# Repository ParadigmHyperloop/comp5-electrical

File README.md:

# comp5-electrical
All schematics and layouts in KiCad, plus some simulations https://paradigmhyperloop.com

License
See the LICENSE for full licensing details.

In summary, (you still need to read the whole thing), these boards are for Paradigm, and Paradigm only. It is shared with the world for the benefit of observers and potential Paradigm team members. If you wish to utilize these designs in any way, you must contact us first and receive written permission to utilize the designs for the purpose you require.

We don't want to be restrictive, and we will almost certainly grant you permission, but we want to know what you are using our designs for, and we want to make sure you are using them correctly and safely.

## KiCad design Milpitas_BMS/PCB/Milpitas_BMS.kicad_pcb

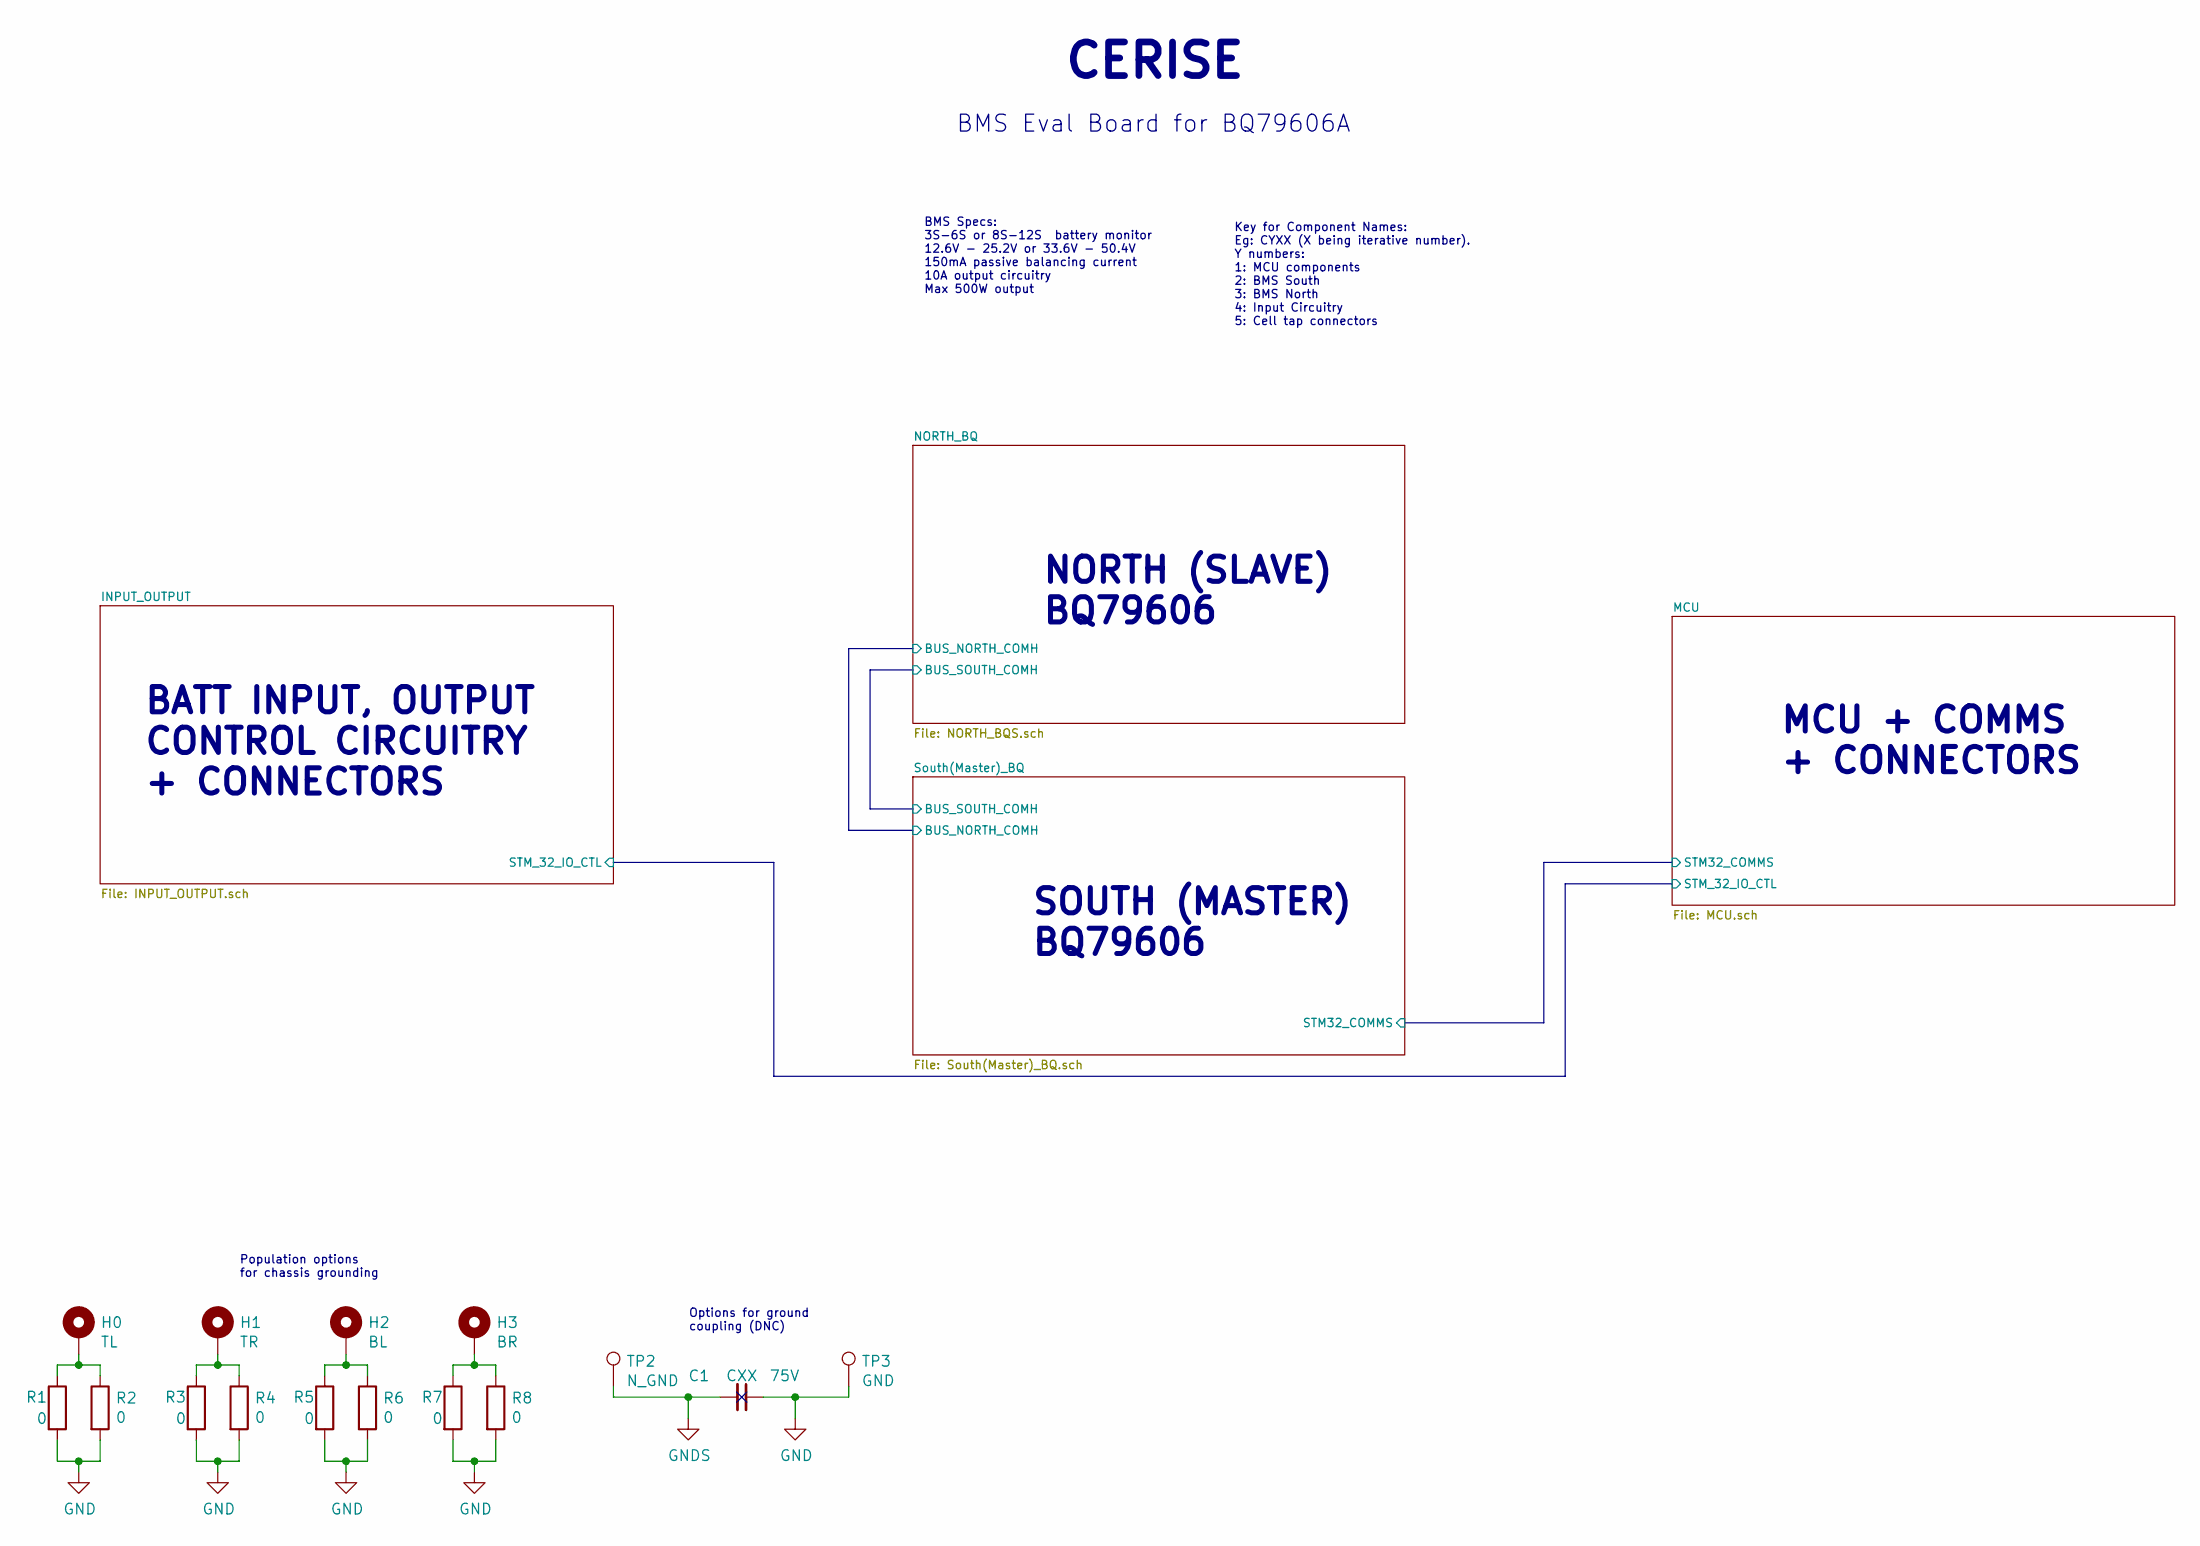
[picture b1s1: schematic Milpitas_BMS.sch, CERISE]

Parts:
C1: CXX; C_0603_1608Metric; Voltage 75V; Digikey 399-7880-1-ND
H0: TL; MountingHole_2.7mm_M2.5_Pad_Via
H1: TR; MountingHole_2.7mm_M2.5_Pad_Via
H2: BL; MountingHole_2.7mm_M2.5_Pad_Via
H3: BR; MountingHole_2.7mm_M2.5_Pad_Via
R1, R2, R3, R4, R5, R6, R7, R8: 0; R_0603_1608Metric; Digikey 311-0.0GRCT-ND
TP2: N_GND; R_1206_3216Metric; Digikey A106146CT-ND
TP3: GND; R_1206_3216Metric; Digikey A106146CT-ND

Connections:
GNDS: C1.2, TP2.1; also elsewhere on the board
unnamed: H0.1, R1.1, R2.1
unnamed: H1.1, R3.1, R4.1
unnamed: H2.1, R5.1, R6.1
unnamed: H3.1, R7.1, R8.1

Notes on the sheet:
SOUTH (MASTER) BQ79606
BATT INPUT, OUTPUT CONTROL CIRCUITRY + CONNECTORS
MCU + COMMS + CONNECTORS
NORTH (SLAVE) BQ79606
CERISE
BMS Eval Board for BQ79606A
Key for Component Names: Eg: CYXX (X being iterative number). Y numbers: 1: MCU components 2: BMS South 3: BMS North 4: Input Circuitry 5: Cell tap connectors
BMS Specs: 3S-6S or 8S-12S battery monitor 12.6V - 25.2V or 33.6V - 50.4V 150mA passive balancing current 10A output circuitry Max 500W output
Population options for chassis grounding
Options for ground coupling (DNC)

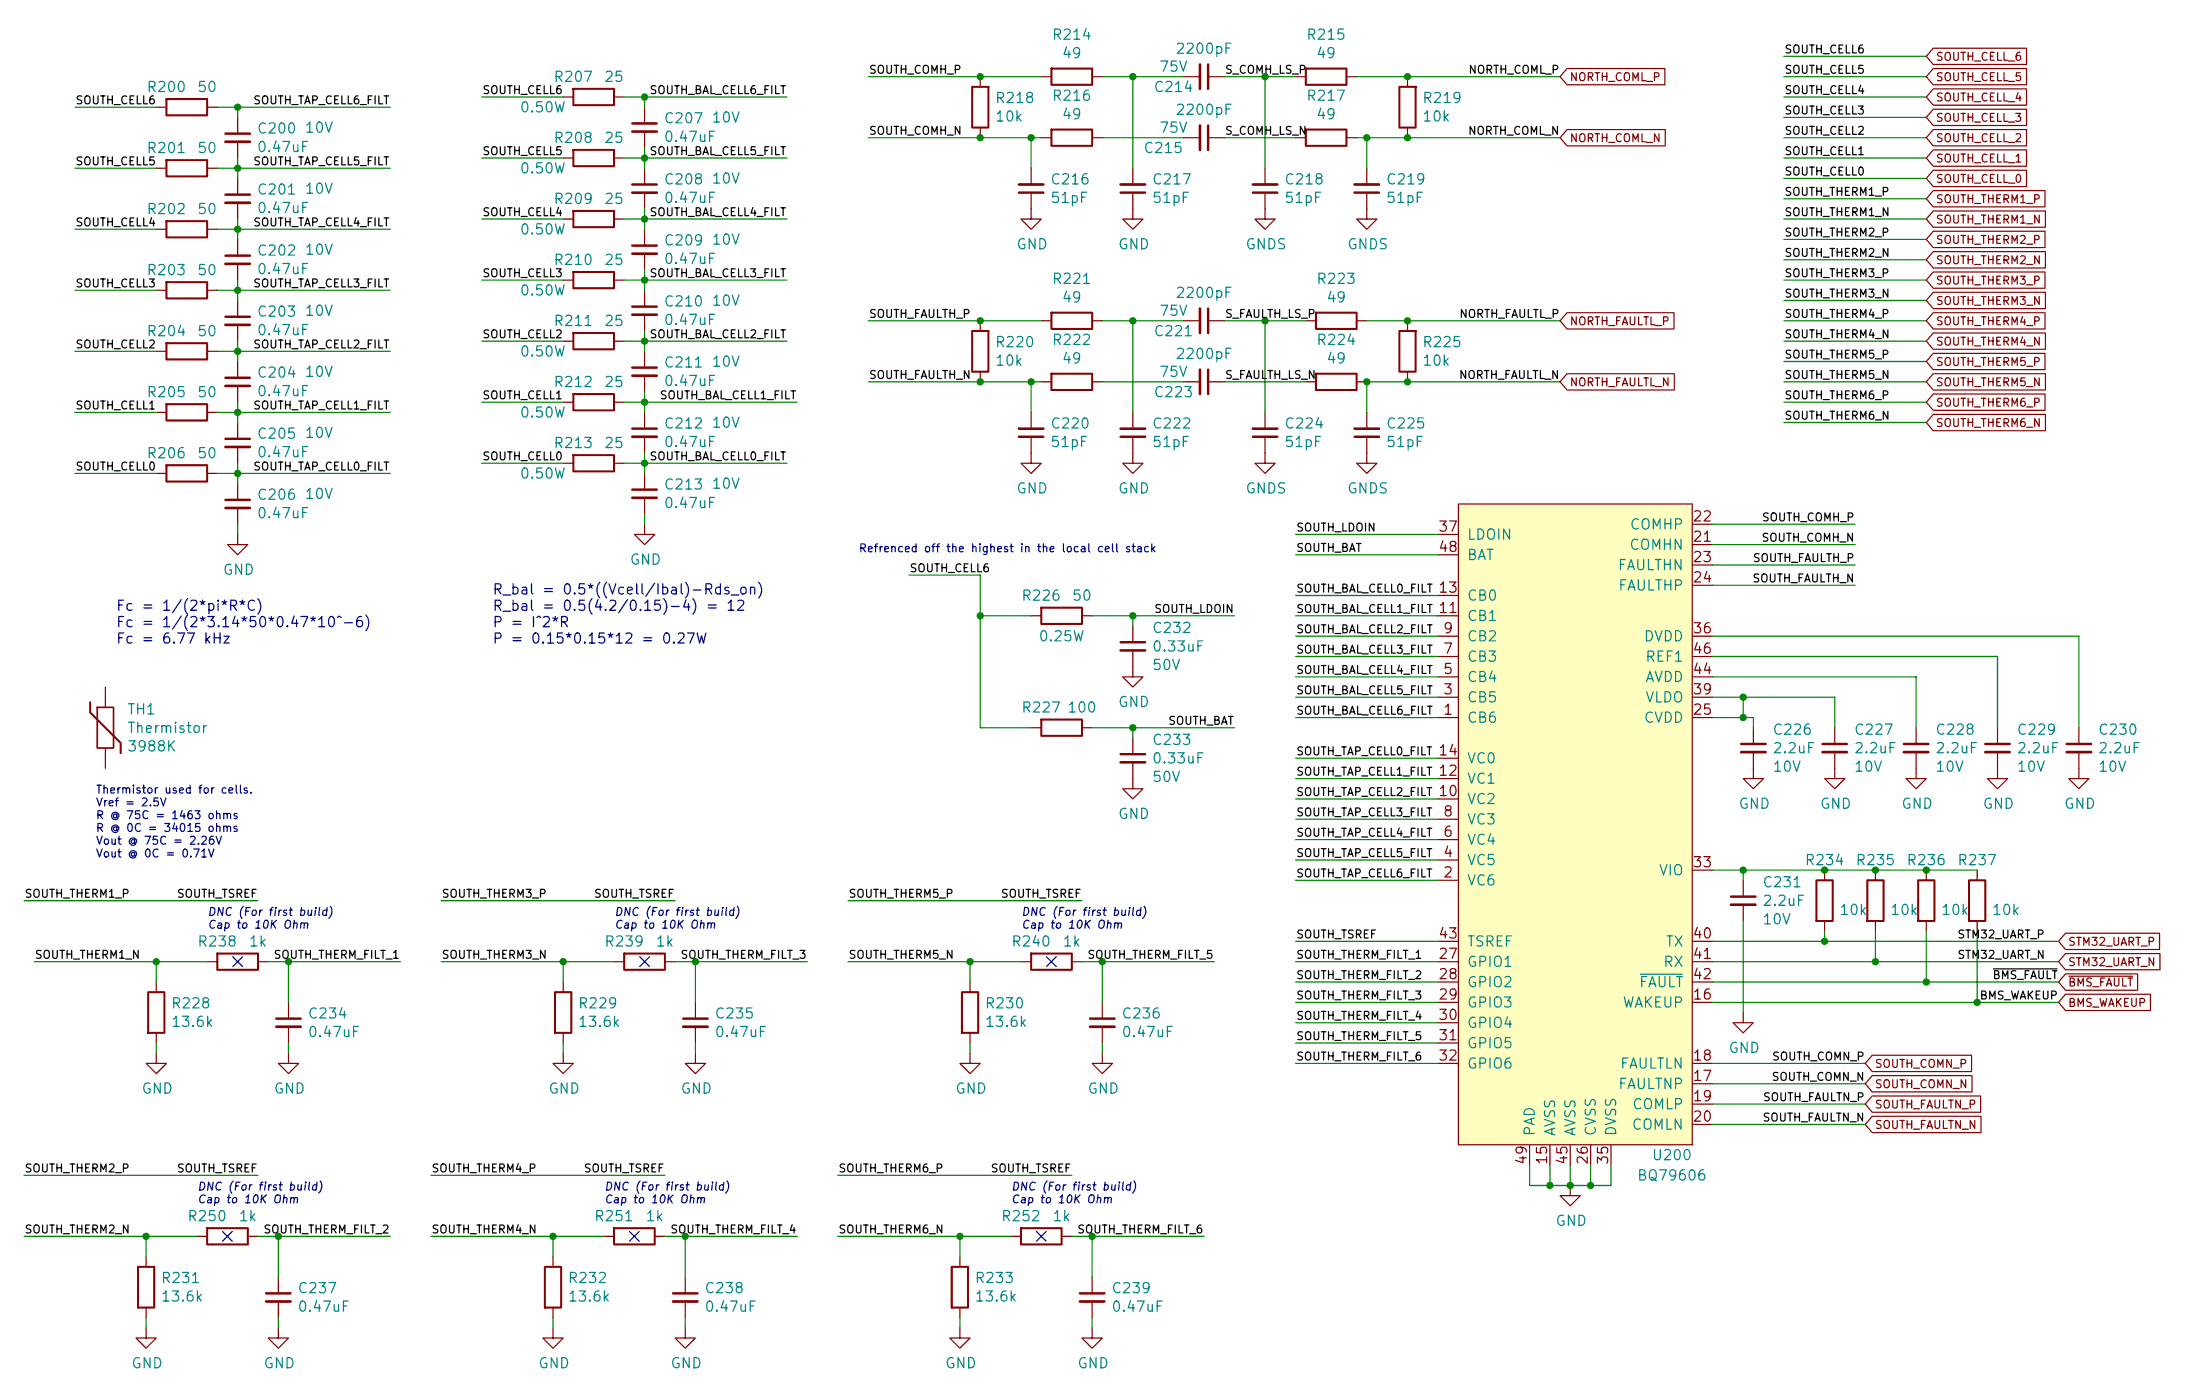
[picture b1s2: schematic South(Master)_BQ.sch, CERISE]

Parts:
C200, C201, C202, C203, C204, C205, C206, C207, C208, C209, C210, C211, C212, C213: 0.47uF; C_0603_1608Metric; Voltage 10V; Digikey 1292-1451-1-ND
C214, C215, C221, C223: 2200pF; C_0603_1608Metric; Voltage 75V; Digikey 399-7880-1-ND
C216, C217, C218, C219, C220, C222, C224, C225: 51pF; C_0603_1608Metric; Digikey 1276-2310-1-ND
C226, C227, C228, C229, C230, C231: 2.2uF; C_0603_1608Metric; Voltage 10V; Digikey 1276-1085-1-ND
C232, C233: 0.33uF; C_0603_1608Metric; Voltage 50V; Digikey 445-7462-1-ND
C234, C235, C236, C237, C238, C239: 0.47uF; C_0603_1608Metric; Digikey 1292-1451-1-ND
R200, R201, R202, R203, R204, R205, R206: 50; R_0603_1608Metric; Digikey 541-3318-1-ND
R207, R208, R209, R210, R211, R212, R213: 25; R_0603_1608Metric; Digikey 541-2654-1-ND
R214, R215, R216, R217, R221, R222, R223, R224: 49; R_0603_1608Metric; Digikey 2019-RN73H1JTTD49R3B25CT-ND
R218, R219, R220, R225, R234, R235, R236, R237: 10k; R_0603_1608Metric; Digikey 311-10KGRCT-ND
R226: 50; R_0603_1608Metric; Digikey 541-2655-1-ND
R227: 100; R_0603_1608Metric; Digikey 311-100HRCT-ND
R228, R229, R230, R231, R232, R233: 13.6k; R_0603_1608Metric; Digikey RMCF0603FT13K7CT-ND
R238, R239, R240, R250, R251, R252: 1k; R_0603_1608Metric; Digikey 311-1.0KGRCT-ND
TH1: Thermistor; Digikey 495-2149-ND
U200: BQ79606; LQFP-48-1EP_7x7mm_P0.5mm_EP3.6x3.6mm_ThermalVias; Digikey 296-BQ79606APHPTQ1CT-ND

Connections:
/South(Master)_BQ/SOUTH_BAL_CELL0_FILT: C212.2, C213.1, R213.1, U200.13 (CB0)
/South(Master)_BQ/SOUTH_BAL_CELL1_FILT: C211.2, C212.1, R212.1, U200.11 (CB1)
/South(Master)_BQ/SOUTH_BAL_CELL2_FILT: C210.2, C211.1, R211.1, U200.9 (CB2)
/South(Master)_BQ/SOUTH_BAL_CELL3_FILT: C209.2, C210.1, R210.1, U200.7 (CB3)
/South(Master)_BQ/SOUTH_BAL_CELL4_FILT: C208.2, C209.1, R209.1, U200.5 (CB4)
/South(Master)_BQ/SOUTH_BAL_CELL5_FILT: C207.2, C208.1, R208.1, U200.3 (CB5)
/South(Master)_BQ/SOUTH_BAL_CELL6_FILT: C207.1, R207.1, U200.1 (CB6)
/South(Master)_BQ/SOUTH_BAT: C233.1, R227.1, U200.48 (BAT)
/South(Master)_BQ/SOUTH_COMH_N: C216.2, R216.2, R218.1, U200.21 (COMHN)
/South(Master)_BQ/SOUTH_COMH_P: R214.2, R218.2, U200.22 (COMHP)
/South(Master)_BQ/SOUTH_FAULTH_N: C220.2, R220.1, R222.2, U200.24 (FAULTHP)
/South(Master)_BQ/SOUTH_FAULTH_P: R220.2, R221.2, U200.23 (FAULTHN)
/South(Master)_BQ/SOUTH_LDOIN: C232.1, R226.1, U200.37 (LDOIN)
/South(Master)_BQ/SOUTH_TAP_CELL0_FILT: C205.2, C206.1, R206.1, U200.14 (VC0)
/South(Master)_BQ/SOUTH_TAP_CELL1_FILT: C204.2, C205.1, R205.1, U200.12 (VC1)
/South(Master)_BQ/SOUTH_TAP_CELL2_FILT: C203.2, C204.1, R204.1, U200.10 (VC2)
/South(Master)_BQ/SOUTH_TAP_CELL3_FILT: C202.2, C203.1, R203.1, U200.8 (VC3)
/South(Master)_BQ/SOUTH_TAP_CELL4_FILT: C201.2, C202.1, R202.1, U200.6 (VC4)
/South(Master)_BQ/SOUTH_TAP_CELL5_FILT: C200.2, C201.1, R201.1, U200.4 (VC5)
/South(Master)_BQ/SOUTH_TAP_CELL6_FILT: C200.1, R200.1, U200.2 (VC6)
/South(Master)_BQ/SOUTH_THERM_FILT_1: C234.1, R238.1, U200.27 (GPIO1)
/South(Master)_BQ/SOUTH_THERM_FILT_2: C237.1, R250.1, U200.28 (GPIO2)
/South(Master)_BQ/SOUTH_THERM_FILT_3: C235.1, R239.1, U200.29 (GPIO3)
/South(Master)_BQ/SOUTH_THERM_FILT_4: C238.1, R251.1, U200.30 (GPIO4)
/South(Master)_BQ/SOUTH_THERM_FILT_5: C236.1, R240.1, U200.31 (GPIO5)
/South(Master)_BQ/SOUTH_THERM_FILT_6: C239.1, R252.1, U200.32 (GPIO6)
/South(Master)_BQ/S_COMH_LS_N: C215.1, R217.2
/South(Master)_BQ/S_COMH_LS_P: C214.1, C218.2, R215.2
/South(Master)_BQ/S_FAULTH_LS_N: C223.1, R224.2
/South(Master)_BQ/S_FAULTH_LS_P: C221.1, C224.2, R223.2
BMS_WAKEUP: R237.2, U200.16 (WAKEUP); also elsewhere on the board
GNDS: C218.1, C219.1, C224.1, C225.1; also elsewhere on the board
NORTH_COML_N: C219.2, R217.1, R219.1; also elsewhere on the board
NORTH_COML_P: R215.1, R219.2; also elsewhere on the board
NORTH_FAULTL_N: C225.2, R224.1, R225.1; also elsewhere on the board
NORTH_FAULTL_P: R223.1, R225.2; also elsewhere on the board
unnamed: C214.2, C217.2, R214.1
unnamed: C215.2, R216.1
unnamed: C221.2, C222.2, R221.1
unnamed: C223.2, R222.1
unnamed: C226.1, C227.1, U200.25 (CVDD), U200.39 (VLDO)
unnamed: C228.1, U200.44 (AVDD)
unnamed: C229.1, U200.46 (REF1)
unnamed: C230.1, U200.36 (DVDD)
unnamed: C231.1, R234.1, R235.1, R236.1, R237.1, U200.33 (VIO)
SOUTH_CELL_0: R206.2, R213.2; also elsewhere on the board
SOUTH_CELL_1: R205.2, R212.2; also elsewhere on the board
SOUTH_CELL_2: R204.2, R211.2; also elsewhere on the board
SOUTH_CELL_3: R203.2, R210.2; also elsewhere on the board
SOUTH_CELL_4: R202.2, R209.2; also elsewhere on the board
SOUTH_CELL_5: R201.2, R208.2; also elsewhere on the board
SOUTH_CELL_6: R200.2, R207.2, R226.2, R227.2; also elsewhere on the board
SOUTH_COMN_N: U200.17 (FAULTNP); also elsewhere on the board
SOUTH_COMN_P: U200.18 (FAULTLN); also elsewhere on the board
SOUTH_FAULTN_N: U200.20 (COMLN); also elsewhere on the board
SOUTH_FAULTN_P: U200.19 (COMLP); also elsewhere on the board
SOUTH_THERM1_N: R228.1, R238.2; also elsewhere on the board
SOUTH_THERM1_P: U200.43 (TSREF); also elsewhere on the board
SOUTH_THERM2_N: R231.1, R250.2; also elsewhere on the board
SOUTH_THERM3_N: R229.1, R239.2; also elsewhere on the board
SOUTH_THERM4_N: R232.1, R251.2; also elsewhere on the board
SOUTH_THERM5_N: R230.1, R240.2; also elsewhere on the board
SOUTH_THERM6_N: R233.1, R252.2; also elsewhere on the board
STM32_UART_N: R235.2, U200.41 (RX); also elsewhere on the board
STM32_UART_P: R234.2, U200.40 (TX); also elsewhere on the board
~BMS_FAULT: R236.2, U200.42 (~FAULT); also elsewhere on the board

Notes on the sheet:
R_bal = 0.5*((Vcell/Ibal)-Rds_on) R_bal = 0.5(4.2/0.15)-4) = 12 P = I^2*R P = 0.15*0.15*12 = 0.27W
DNC (For first build) Cap to 10K Ohm
Fc = 1/(2*pi*R*C) Fc = 1/(2*3.14*50*0.47*10^-6) Fc = 6.77 kHz
Thermistor used for cells. Vref = 2.5V R @ 75C = 1463 ohms R @ 0C = 34015 ohms Vout @ 75C = 2.26V Vout @ 0C = 0.71V
Refrenced off the highest in the local cell stack

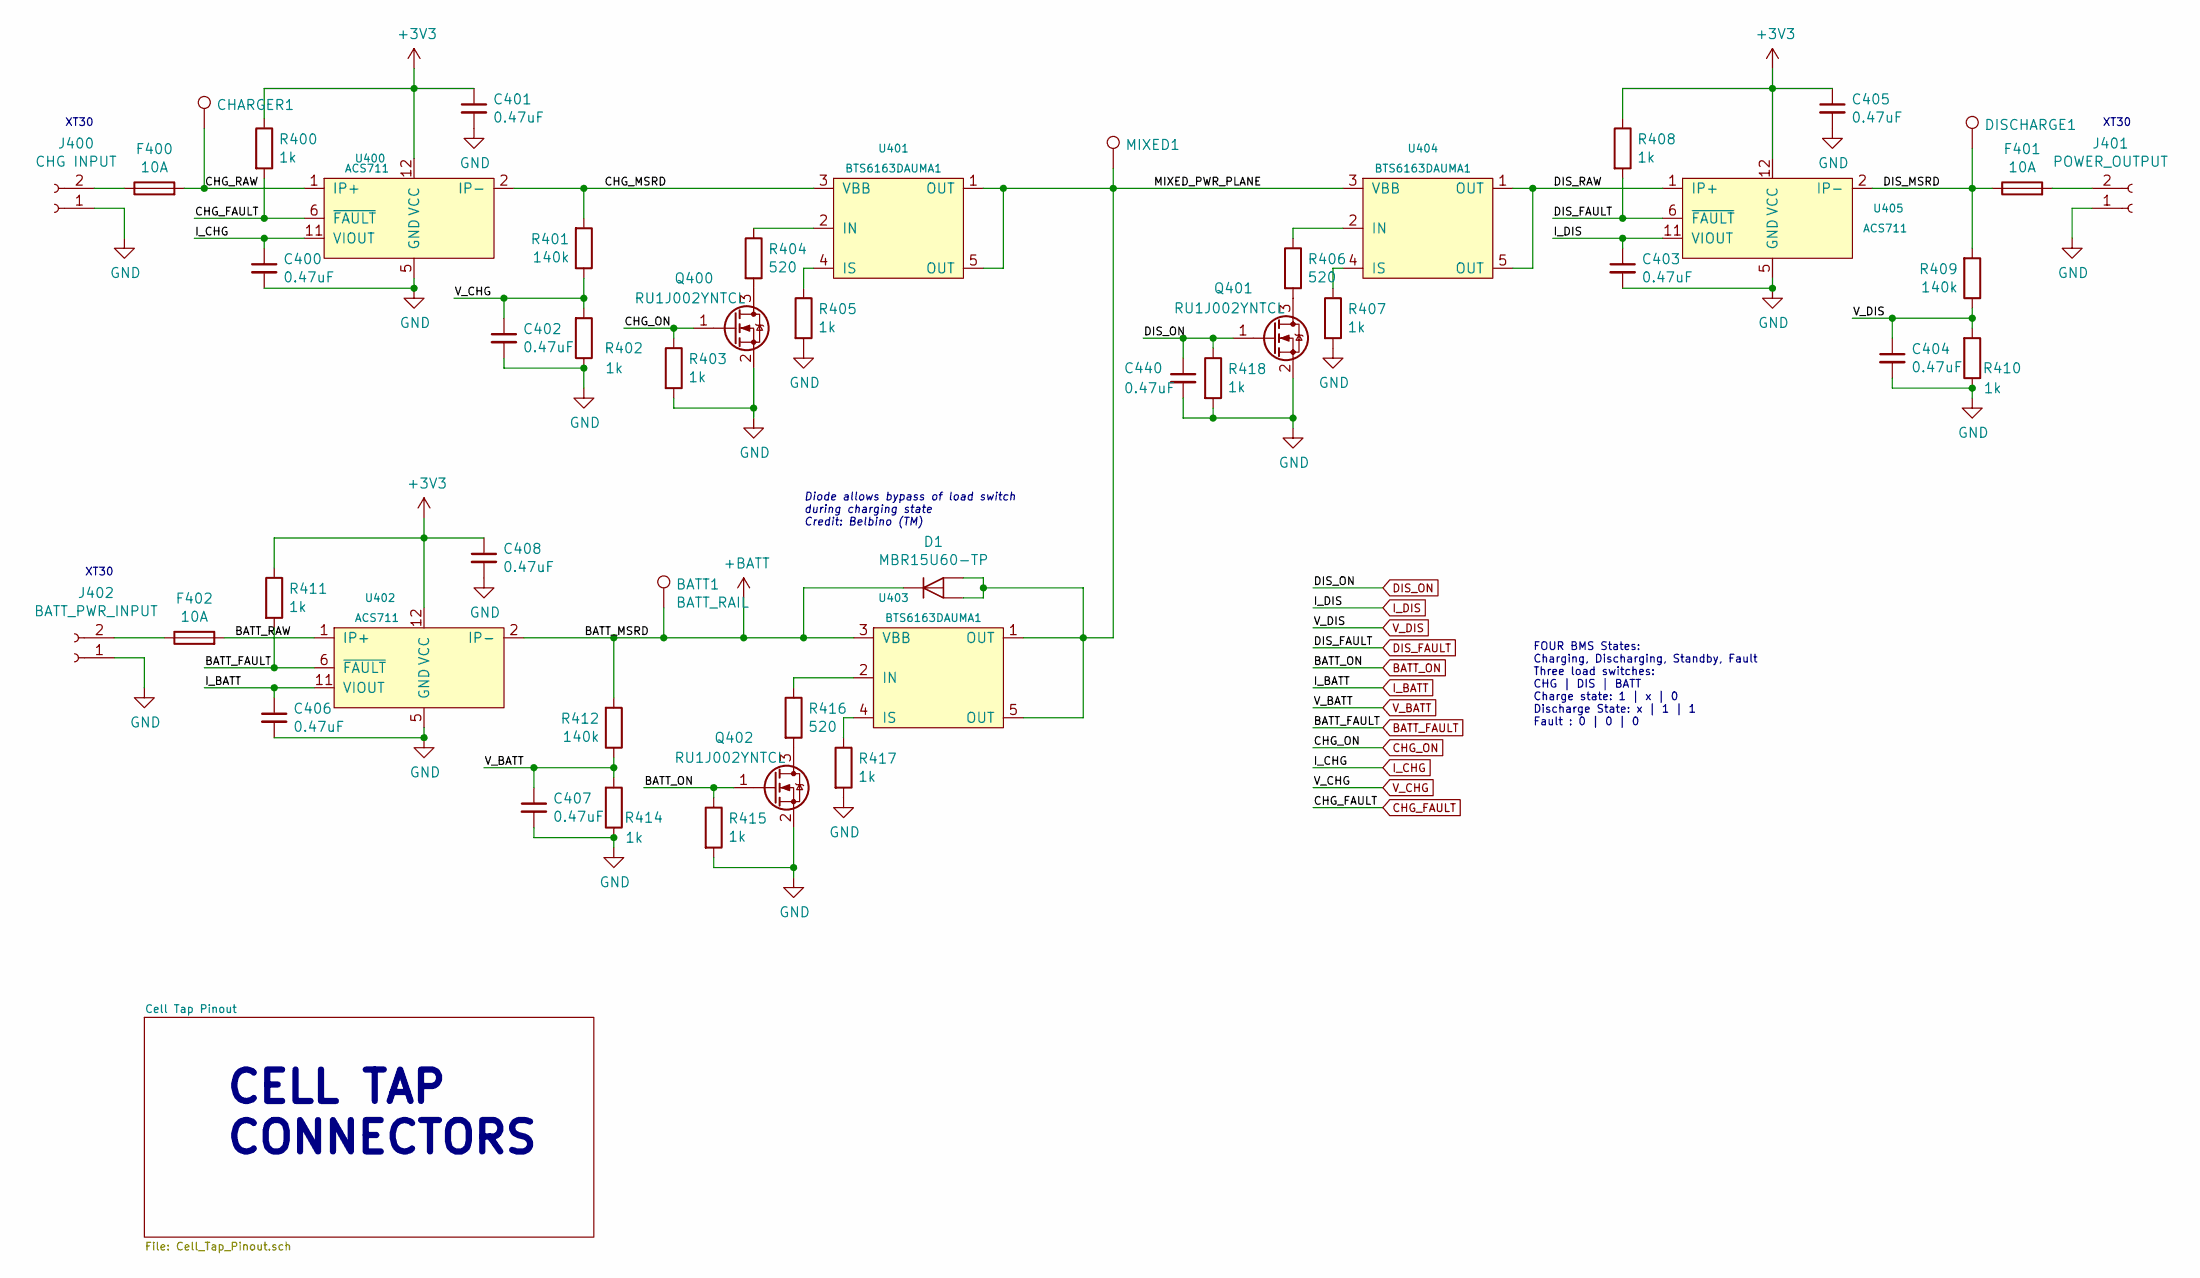
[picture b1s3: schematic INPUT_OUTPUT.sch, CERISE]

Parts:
BATT1: BATT_RAIL; TestPoint_Pad_D1.0mm
C400, C401, C402, C403, C404, C405, C406, C407, C408, C440: 0.47uF; C_0603_1608Metric; Voltage 10V; Digikey 1292-1451-1-ND
CHARGER1: CHARGER; TestPoint_Pad_D1.0mm
D1: MBR15U60-TP; TO-277A; Digikey MBR15U60-TPMSTR-ND
DISCHARGE1: DISCHARGE; TestPoint_Pad_D1.0mm
F400, F401, F402: 10A; Fuse_1206_3216Metric; Digikey 486-1686-1-ND
J400: CHG INPUT; XT30-RIGHT-ANGLE
J401: POWER_OUTPUT; XT30-RIGHT-ANGLE
J402: BATT_PWR_INPUT; XT30-RIGHT-ANGLE
MIXED1: POWER_MIX; TestPoint_Pad_D1.0mm
Q400, Q401, Q402: RU1J002YNTCL; SOT-323_SC-70; Digikey RU1J002YNTCLCT-ND
R400, R402, R403, R405, R407, R408, R410, R411, R414, R415, R417, R418: 1k; R_0603_1608Metric; Digikey 311-1.0KGRCT-ND
R401, R409, R412: 140k; R_0603_1608Metric; Digikey RMCF0603FT140KCT-ND
R404, R406, R416: 520; R_0603_1608Metric; Digikey A129685CT-ND
U400, U402, U405: ACS711; Allegro_QFN-12-10-1EP_3x3mm_P0.5mm; Digikey 620-1483-1-ND
U401, U403, U404: BTS6163DAUMA1; TO-252-5_TabPin3; Digikey BTS6163DAUMA1CT-ND

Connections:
+BATT: BATT1.1, D1.3 (K), R412.2, U402.2 (IP-), U403.3 (VBB); also elsewhere on the board
/INPUT_OUTPUT/BATT_RAW: F402.2, U402.1 (IP+)
/INPUT_OUTPUT/CHG_MSRD: R401.2, U400.2 (IP-), U401.3 (VBB)
/INPUT_OUTPUT/CHG_RAW: CHARGER1.1, F400.2, U400.1 (IP+); also elsewhere on the board
/INPUT_OUTPUT/DIS_MSRD: DISCHARGE1.1, F401.1, R409.2, U405.2 (IP-); also elsewhere on the board
/INPUT_OUTPUT/DIS_RAW: U404.1 (OUT), U404.5 (OUT), U405.1 (IP+)
/INPUT_OUTPUT/MIXED_PWR_PLANE: D1.1 (A), D1.2 (A), MIXED1.1, U401.1 (OUT), U401.5 (OUT), U403.1 (OUT), U403.5 (OUT), U404.3 (VBB); also elsewhere on the board
BATT_FAULT: R411.2, U402.6 (~FAULT); also elsewhere on the board
BATT_ON: Q402.1 (G), R415.1; also elsewhere on the board
CHG_FAULT: R400.2, U400.6 (~FAULT); also elsewhere on the board
CHG_ON: Q400.1 (G), R403.1; also elsewhere on the board
DIS_FAULT: R408.2, U405.6 (~FAULT); also elsewhere on the board
DIS_ON: C440.1, Q401.1 (G), R418.1; also elsewhere on the board
I_BATT: C406.1, U402.11 (VIOUT); also elsewhere on the board
I_CHG: C400.1, U400.11 (VIOUT); also elsewhere on the board
I_DIS: C403.1, U405.11 (VIOUT); also elsewhere on the board
unnamed 171: F400.1, J400.2; also elsewhere on the board
unnamed 172: F401.2, J401.2; also elsewhere on the board
unnamed 173: F402.1, J402.2; also elsewhere on the board
unnamed: Q400.3 (D), R404.2
unnamed: Q401.3 (D), R406.2
unnamed: Q402.3 (D), R416.2
unnamed: R404.1, U401.2 (IN)
unnamed: R405.1, U401.4 (IS)
unnamed: R406.1, U404.2 (IN)
unnamed: R407.1, U404.4 (IS)
unnamed: R416.1, U403.2 (IN)
unnamed: R417.1, U403.4 (IS)
V_BATT: C407.1, R412.1, R414.2; also elsewhere on the board
V_CHG: C402.1, R401.1, R402.2; also elsewhere on the board
V_DIS: C404.1, R409.1, R410.2; also elsewhere on the board

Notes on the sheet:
Diode allows bypass of load switch during charging state Credit: Belbino (TM)
FOUR BMS States: Charging, Discharging, Standby, Fault Three load switches: CHG | DIS | BATT Charge state: 1 | x | 0 Discharge State: x | 1 | 1 Fault : 0 | 0 | 0
CELL TAP CONNECTORS
XT30

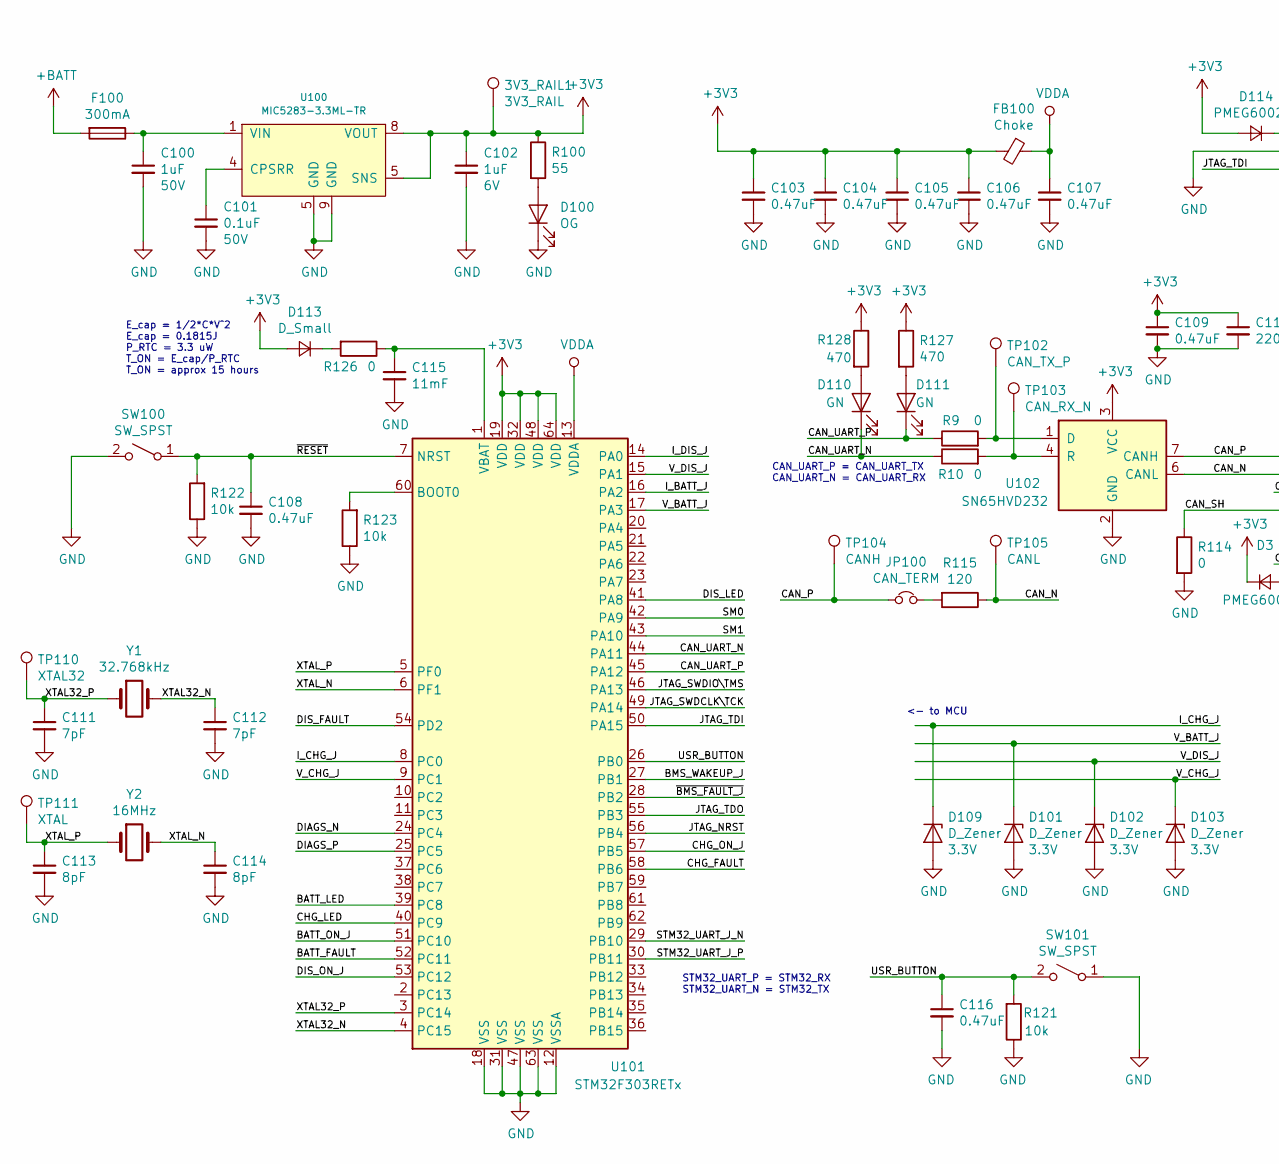
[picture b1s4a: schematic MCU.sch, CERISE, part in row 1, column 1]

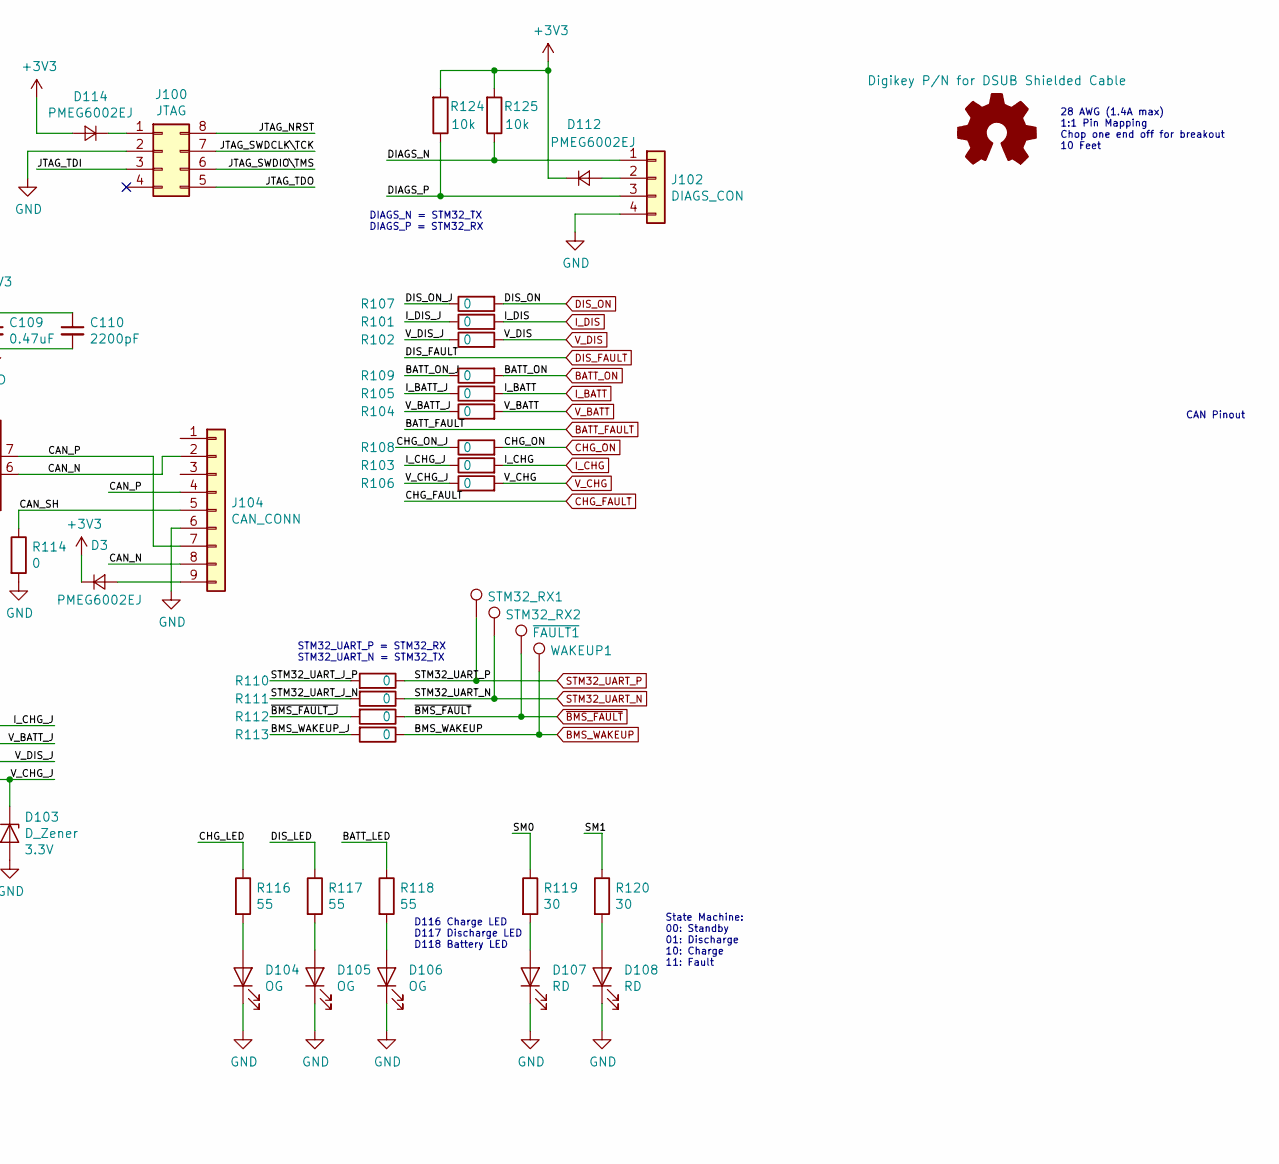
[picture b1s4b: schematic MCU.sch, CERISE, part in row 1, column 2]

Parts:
3V3_RAIL1: 3V3_RAIL; TestPoint_Pad_D1.0mm
C100: 1uF; C_0603_1608Metric; Voltage 50V; Digikey 1276-1860-1-ND
C101: 0.1uF; C_0603_1608Metric; Voltage 50V; Digikey 399-7845-1-ND
C102: 1uF; C_0603_1608Metric; Voltage 6V; Digikey 1276-1860-1-ND
C103, C104, C105, C106, C107, C108, C109, C116: 0.47uF; C_0603_1608Metric; Digikey 1292-1451-1-ND
C110: 2200pF; C_0603_1608Metric; Digikey 399-7880-1-ND
C111, C112: 7pF; C_0603_1608Metric; Digikey 490-11478-1-ND
C113, C114: 8pF; C_0603_1608Metric; Digikey 490-9670-1-ND
C115: 11mF; C_1210_3225Metric; Digikey 728-1127-1-ND
D3, D112, D114: PMEG6002EJ; D_SOD-323F; Digikey 1727-5214-1-ND
D100, D104, D105, D106: OG; LED_0603_1608Metric; Digikey SML-D12D1WT86CT-ND
D101, D102, D103, D109: D_Zener; D_SOD-323F; Voltage 3.3V; Digikey MM3Z3V3BCT-ND
D107, D108: RD; LED_0603_1608Metric; Digikey 732-4978-1-ND
D110, D111: GN; LED_0603_1608Metric; Digikey 732-4980-1-ND
D113: D_Small; D_SOD-323F; Digikey 1727-5214-1-ND
F100: 300mA; Fuse_0603_1608Metric; Digikey 507-1087-1-ND
FB100: Choke; L_0603_1608Metric; Digikey 445-8672-1-ND
J100: JTAG; PinHeader_2x04_P1.27mm_Vertical; Digikey 2057-HPH2-A-08-UA-ND
J102: DIAGS_CON; PinHeader_2x02_P1.27mm_Vertical; Digikey 2057-HPH2-A-04-UA-ND
J104: CAN_CONN; DSUB-9_Female_Horizontal_P2.77x2.84mm_EdgePinOffset4.94mm_H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; Digikey A132511-ND
JP100: CAN_TERM; SolderJumper-2_P1.3mm_Open_TrianglePad1.0x1.5mm
R9, R10, R101, R102, R103, R104, R105, R106, R107, R108, R109, R110, R111, R112, R113, R114, R126: 0; R_0603_1608Metric; Digikey 311-0.0GRCT-ND
R100, R116, R117, R118: 55; R_0603_1608Metric; Digikey A129673CT-ND
R115: 120; R_0603_1608Metric; Digikey 311-120HRCT-ND
R119, R120: 30; R_0603_1608Metric; Digikey 311-30GRCT-ND
R121, R122, R123, R124, R125: 10k; R_0603_1608Metric; Digikey 311-10KGRCT-ND
R127, R128: 470; R_0603_1608Metric; Digikey 311-470GRCT-ND
STM32_RX1: BMS_UART_TX; TestPoint_Pad_D1.0mm
STM32_RX2: BMS_UART_RX; TestPoint_Pad_D1.0mm
SW100, SW101: SW_SPST; B3U-1100P; Digikey SW1020CT-ND
TP102: CAN_TX_P; TestPoint_Pad_D1.0mm
TP103: CAN_RX_N; TestPoint_Pad_D1.0mm; Digikey 36-5003-ND
TP104: CANH; TestPoint_Bridge_Pitch2.54mm_Drill1.0mm; Digikey 36-5003-ND
TP105: CANL; TestPoint_Bridge_Pitch2.54mm_Drill1.0mm; Digikey 36-5003-ND
TP110: XTAL32; TestPoint_Pad_D1.0mm
TP111: XTAL; TestPoint_Pad_D1.0mm
U100: MIC5283-3.3ML-TR; MLF-8-1EP_3x3mm_P0.65mm_EP1.55x2.3mm_ThermalVias; Digikey MIC5283-3.3YML-CT-ND
U101: STM32F303RETx; LQFP-64_10x10mm_P0.5mm
U102: SN65HVD232; SOIC-8_3.9x4.9mm_P1.27mm
WAKEUP1: BMS_WAKEUP; TestPoint_Pad_D1.0mm
Y1: 32.768kHz; FC-135; Digikey FC-13532.7680KA-AG-ND
Y2: 16MHz; NX3225GB; Digikey 644-1233-1-ND
~FAULT1: BMS_FAULT; TestPoint_Pad_D1.0mm

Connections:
+BATT: F100.2; also elsewhere on the board
/MCU/BATT_LED: R118.1, U101.39 (PC8)
/MCU/BATT_ON_J: R109.1, U101.51 (PC10)
/MCU/BMS_WAKEUP_J: R113.2, U101.27 (PB1)
/MCU/CAN_N: J104.2, J104.8, R115.1, TP105.1, U102.6 (CANL)
/MCU/CAN_P: J104.4, J104.7, JP100.1, TP104.1, U102.7 (CANH)
/MCU/CAN_SH: J104.5, R114.1
/MCU/CAN_UART_N: D110.1 (K), R10.1, U101.44 (PA11)
/MCU/CAN_UART_P: D111.1 (K), R9.1, U101.45 (PA12)
/MCU/CHG_LED: R116.1, U101.40 (PC9)
/MCU/CHG_ON_J: R108.1, U101.57 (PB5)
/MCU/DIAGS_N: J102.1, R125.1, U101.24 (PC4)
/MCU/DIAGS_P: J102.3, R124.1, U101.25 (PC5)
/MCU/DIS_LED: R117.1, U101.41 (PA8)
/MCU/DIS_ON_J: R107.1, U101.53 (PC12)
/MCU/I_BATT_J: R105.1, U101.16 (PA2)
/MCU/I_CHG_J: D109.1 (K), R103.1, U101.8 (PC0)
/MCU/I_DIS_J: R101.1, U101.14 (PA0)
/MCU/JTAG_NRST: J100.8, U101.56 (PB4)
/MCU/JTAG_SWDCLK\TCK: J100.7, U101.49 (PA14)
/MCU/JTAG_SWDIO\TMS: J100.6, U101.46 (PA13)
/MCU/JTAG_TDI: J100.3, U101.50 (PA15)
/MCU/JTAG_TDO: J100.5, U101.55 (PB3)
/MCU/SM0: R119.1, U101.42 (PA9)
/MCU/SM1: R120.1, U101.43 (PA10)
/MCU/STM32_UART_J_N: R111.2, U101.29 (PB10)
/MCU/STM32_UART_J_P: R110.2, U101.30 (PB11)
/MCU/USR_BUTTON: C116.1, R121.2, SW101.2 (B), U101.26 (PB0)
/MCU/V_BATT_J: D101.1 (K), R104.1, U101.17 (PA3)
/MCU/V_CHG_J: D103.1 (K), R106.1, U101.9 (PC1)
/MCU/V_DIS_J: D102.1 (K), R102.1, U101.15 (PA1)
/MCU/XTAL32_N: C112.1, U101.4 (PC15), Y1.2
/MCU/XTAL32_P: C111.1, TP110.1, U101.3 (PC14), Y1.1
/MCU/XTAL_N: C114.1, U101.6 (PF1), Y2.2
/MCU/XTAL_P: C113.1, TP111.1, U101.5 (PF0), Y2.1
/MCU/~BMS_FAULT_J: R112.2, U101.28 (PB2)
/MCU/~RESET: C108.1, R122.2, SW100.1 (A), U101.7 (NRST)
BATT_FAULT: U101.52 (PC11); also elsewhere on the board
BATT_ON: R109.2; also elsewhere on the board
BMS_WAKEUP: R113.1, WAKEUP1.1; also elsewhere on the board
CHG_FAULT: U101.58 (PB6); also elsewhere on the board
CHG_ON: R108.2; also elsewhere on the board
DIS_FAULT: U101.54 (PD2); also elsewhere on the board
DIS_ON: R107.2; also elsewhere on the board
I_BATT: R105.2; also elsewhere on the board
I_CHG: R103.2; also elsewhere on the board
I_DIS: R101.2; also elsewhere on the board
unnamed: C100.1, F100.1, U100.1 (VIN)
unnamed: C101.1, U100.4 (CPSRR)
unnamed: C115.1, R126.1, U101.1 (VBAT)
unnamed: D3.2 (A), J104.9
unnamed: D100.2 (A), R100.2
unnamed: D104.2 (A), R116.2
unnamed: D105.2 (A), R117.2
unnamed: D106.2 (A), R118.2
unnamed: D107.2 (A), R119.2
unnamed: D108.2 (A), R120.2
unnamed: D110.2 (A), R128.2
unnamed: D111.2 (A), R127.2
unnamed: D112.2 (A), J102.2
unnamed: D113.1 (K), R126.2
unnamed: D114.1 (K), J100.1
unnamed: JP100.2, R115.2
unnamed: R9.2, TP102.1, U102.1 (D)
unnamed: R10.2, TP103.1, U102.4 (R)
unnamed: R123.2, U101.60 (BOOT0)
STM32_UART_N: R111.1, STM32_RX2.1; also elsewhere on the board
STM32_UART_P: R110.1, STM32_RX1.1; also elsewhere on the board
VDDA: C107.1, FB100.1, U101.13 (VDDA)
V_BATT: R104.2; also elsewhere on the board
V_CHG: R106.2; also elsewhere on the board
V_DIS: R102.2; also elsewhere on the board
~BMS_FAULT: R112.1, ~FAULT1.1; also elsewhere on the board

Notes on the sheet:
D116 Charge LED D117 Discharge LED D118 Battery LED
State Machine: 00: Standby 01: Discharge 10: Charge 11: Fault
<- to MCU
28 AWG (1.4A max) 1:1 Pin Mapping Chop one end off for breakout 10 Feet
E_cap = 1/2*C*V^2 E_cap = 0.1815J P_RTC = 3.3 uW T_ON = E_cap/P_RTC T_ON = approx 15 hours
STM32_UART_P = STM32_RX STM32_UART_N = STM32_TX
CAN_UART_P = CAN_UART_TX CAN_UART_N = CAN_UART_RX
DIAGS_N = STM32_TX DIAGS_P = STM32_RX
CAN Pinout

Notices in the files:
Milpitas_BMS/TI Resources/Example Code/include/bq79606.h:
Copyright (c) 2011-2017 Texas Instruments
